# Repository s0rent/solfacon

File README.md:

# Solfacon
### An efficient fan controller designed for solar powered sustainable / off-grid ventilation

Feature highlights:
* Low-light operation / assisted fan start
* Adjustable stable fan speed - PWM duty cycle calculated based on available voltage and desired fan speed
* Connect the solar panel and fan(s) directly to the controller (includes fan headers for connecting one or two 3-pin or 4-pin 12V PC fans)
* Configuration tool allows for easy adaptation to any fan make and model (default configuration is for Arctic P12 fans)
* LDO / switch mode combo power regulation for efficient power conditioning - fan operation down to ~4V input voltage
* Easy assembly in standard enclosure with stencil for drilling
* Easy to configure, build, modify and hack

Technical specs:
* Solar panel open circuit voltage: 16V ~ 26V
* Recommended max load: 12W (peak)
* Recommended max total fan power rating: 6W (all fans combined)
* Quiescent current: 5mA
* Operating temperature: -20°C to 50°C
* Fan PWM frequency: 25KHz (Intel PC fan spec)
* MCU: ATtiny85 @ 3.3V

Prerequisites:
* Solar panel
* Fan
* Soldering iron for assembling the controller
* Arduino IDE for flashing the MCU
* ISP for flashing the MCU

Read more here and configure your own using the configuration tool:
https://s0rent.github.io/solfacon/

"Low-light operation / assisted fan start" allows fan start and operation in otherwise difficult conditions, such as partial shade, suboptimal panel angle and at dawn/dusk. The photo above is a setup with a 20W panel and one fan (Arctic P12), and the fan is running continuously despite the panel only being partially exposed to faint sunlight right after dawn. In this situation the panel only supplies around 20mA, but the controller design allows it to buffer enough energy to efficiently start the fan and keep it running.

Software used: <br>
* KiCad 6.0
* Arduino IDE 2.2.0 (should be compatible with newer versions as well)
* ATtiny package for Arduino IDE (https://github.com/damellis/attiny)

Hardware used: <br>
* USBtinyISP (it is also possible to use for instance an Arduino as ISP)

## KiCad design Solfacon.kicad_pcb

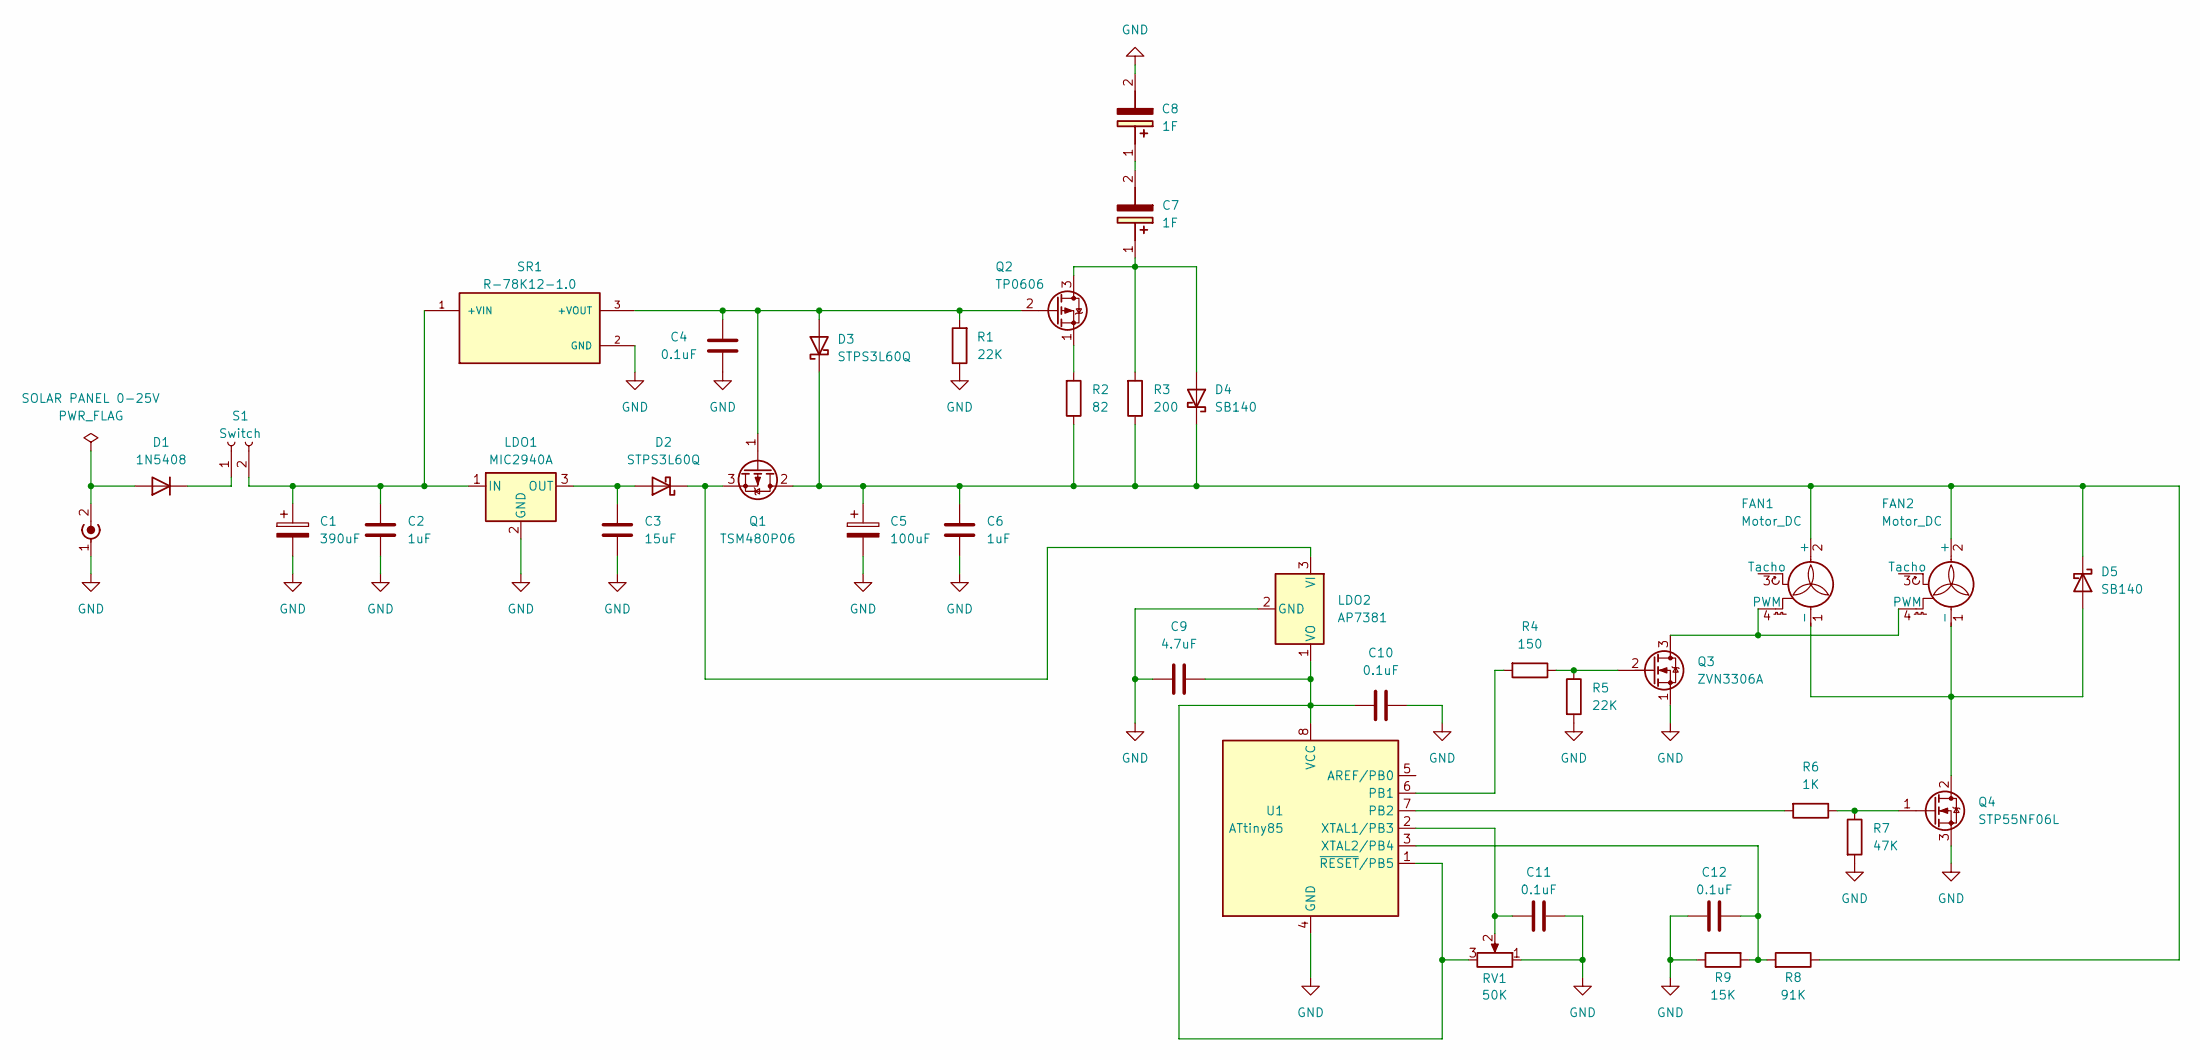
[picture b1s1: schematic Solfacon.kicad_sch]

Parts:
C1: 390uF; CP_Radial_D8.0mm_P3.50mm
C2, C6: 1uF; C_Disc_D4.7mm_W2.5mm_P5.00mm
C3: 15uF; CP_Radial_Tantal_D6.0mm_P2.50mm
C4, C10, C11, C12: 0.1uF; C_Disc_D5.0mm_W2.5mm_P2.50mm
C5: 100uF; CP_Radial_D6.3mm_P2.50mm
C7, C8: 1F; SCMR14L334SSBB0
C9: 4.7uF; CP_Radial_Tantal_D4.5mm_P2.50mm
D1: 1N5408; D_DO-201AD_P4.00mm_Vertical_AnodeUp
D2, D3: STPS3L60Q; D_DO-15_P3.81mm_Vertical_AnodeUp
D4: SB140; D_DO-41_SOD81_P7.62mm_Horizontal
D5: SB140; D_DO-41_SOD81_P3.81mm_Vertical_AnodeUp
FAN1, FAN2: Motor_DC; CONN_SD-47053-001_H10p00_MOL
LDO1: MIC2940A; TO-220-3_Vertical
LDO2: AP7381; TO-92_Inline_Wide
POWER1: SOLAR PANEL 0-25V; TerminalBlock_RND_205-00045_1x02_P5.00mm_Horizontal
Q1: TSM480P06; TO-251-3_Vertical
Q2: TP0606; TO-92_Inline_Wide
Q3: ZVN3306A; TO-92_Inline_Wide
Q4: STP55NF06L; TO-220-3_Vertical
R1, R5: 22K; R_Axial_DIN0207_L6.3mm_D2.5mm_P2.54mm_Vertical
R2: 82; R_Axial_DIN0309_L9.0mm_D3.9mm_P12.70mm_Horizontal
R3: 200; R_Axial_DIN0207_L6.3mm_D2.5mm_P7.62mm_Horizontal
R4: 150; R_Axial_DIN0207_L6.3mm_D2.5mm_P2.54mm_Vertical
R6: 1K; R_Axial_DIN0207_L6.3mm_D2.5mm_P2.54mm_Vertical
R7: 47K; R_Axial_DIN0207_L6.3mm_D2.5mm_P2.54mm_Vertical
R8: 91K; R_Axial_DIN0207_L6.3mm_D2.5mm_P7.62mm_Horizontal
R9: 15K; R_Axial_DIN0207_L6.3mm_D2.5mm_P7.62mm_Horizontal
RV1: 50K; PinHeader_1x03_P2.54mm_Vertical
S1: Conn_01x02_Female; PinHeader_1x02_P2.54mm_Vertical
SR1: R-78K12-1.0; CONV_R-78K12-1.0; PARTREV 0/2023
U1: ATtiny85; DIP-8_W7.62mm

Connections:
unnamed: C1.1, C2.1, LDO1.1 (IN), S1.2, SR1.1 (+VIN)
unnamed: C3.1, D2.2 (A), LDO1.3 (OUT)
unnamed: C4.1, D3.2 (A), Q1.1 (G), Q2.2 (G), R1.2, SR1.3 (+VOUT)
unnamed: C5.1, C6.1, D3.1 (K), D4.1 (K), D5.1 (K), FAN1.2 (+), FAN2.2 (+), Q1.2 (D), R2.1, R3.1, R8.1
unnamed: C7.1 (+), D4.2 (A), Q2.3 (D), R3.2
unnamed: C7.2 (-), C8.1 (+)
unnamed: C9.2, C10.2, LDO2.1 (VO), RV1.3, U1.1 (~RESET/PB5), U1.8 (VCC)
unnamed: C11.1, RV1.2, U1.2 (XTAL1/PB3)
unnamed: C12.1, R8.2, R9.2, U1.3 (XTAL2/PB4)
unnamed: D1.1 (K), S1.1
unnamed: D1.2 (A), POWER1.2 (In)
unnamed: D2.1 (K), LDO2.3 (VI), Q1.3 (S)
unnamed: D5.2 (A), FAN1.1 (-), FAN2.1 (-), Q4.2 (D)
unnamed: FAN1.4 (PWM), FAN2.4 (PWM), Q3.3 (D)
unnamed: Q2.1 (S), R2.2
unnamed: Q3.2 (G), R4.1, R5.1
unnamed: Q4.1 (G), R6.1, R7.1
unnamed: R4.2, U1.6 (PB1)
unnamed: R6.2, U1.7 (PB2)

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
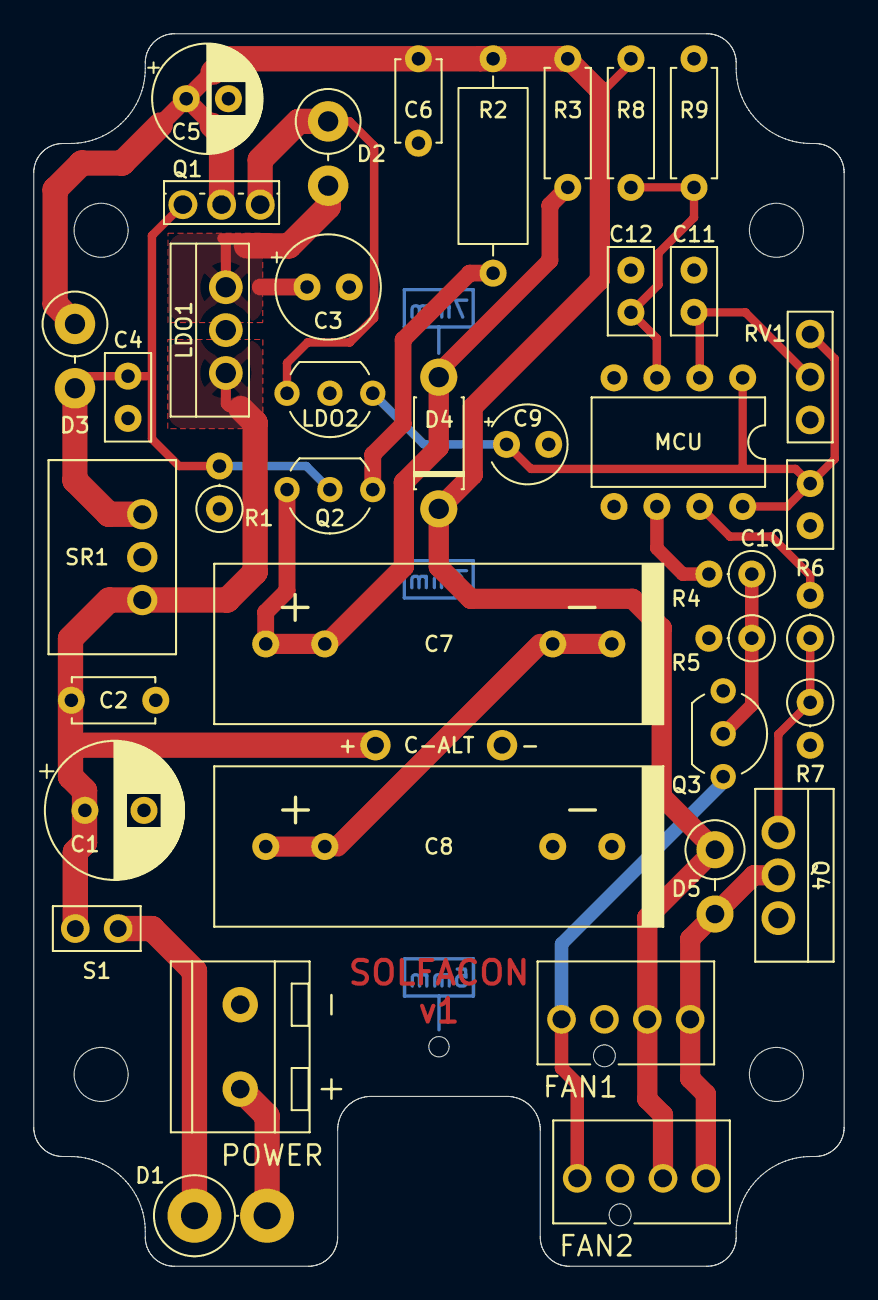
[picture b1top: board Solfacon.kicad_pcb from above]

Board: 2 copper layers, 48.0 x 73.0 mm, 40 parts (0 on the bottom side), 20 nets.

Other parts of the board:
 : MountingHole_2mm

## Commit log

2024-12-23 Adaptive mode config added
2025-01-02 Readme updated
